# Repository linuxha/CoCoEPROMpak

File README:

CoCoEPROMpak 1.0
Copyright 2013 by Mark J. Blair
Distributed under GPLv3

CoCoEPROMpak is a PCB design for an EPROM-based ROM cartridge for the
Tandy/TRS-80 Color Computer. It can accept on 2732, 2764, 27128, 27256
or 27512 EPROM. Board thickness must be 0.062". Gold plating is
preferable to avoid contact oxidation. Board is designed to the
OSHpark design rules for a 2-layer PCB.

When using 27256 or larger EPROMs, the EPROM is divided into 2-4 16k
banks which can be selected with jumper settings. Jumper settings are
also important for 27256 and smaller EPROMs in order to apply the
correct power and control signals to the EPROM.

4k:
    * Install 2732 at U1
    * JP2, JP3 not used
8k:
    * Install 2764 at U2
    * Set JP2 to 1
    * Set JP3 to 1
16k:
    * Install 27128 at U2
    * Set JP2 to 1
    * Set JP3 to 1
32k:
    * Install 27256 at U2
    * Select 16k bank with JP2
    * Set JP3 to 1
64k:
    * Install 27512 at U2
    * Select 16k banks with JP2 and JP3

CoCoEPROMpak is a free hardware design: you can redistribute it and/or
modify it under the terms of the GNU General Public License as
published by the Free Software Foundation, either version 3 of the
License, or (at your option) any later version.

CoCoEPROMpak is distributed in the hope that it will be useful, but
WITHOUT ANY WARRANTY; without even the implied warranty of
MERCHANTABILITY or FITNESS FOR A PARTICULAR PURPOSE. See the GNU
General Public License for more details.

You should have received a copy of the GNU General Public License
along with CoCoEPROMpak. If not, see <http://www.gnu.org/licenses/>.

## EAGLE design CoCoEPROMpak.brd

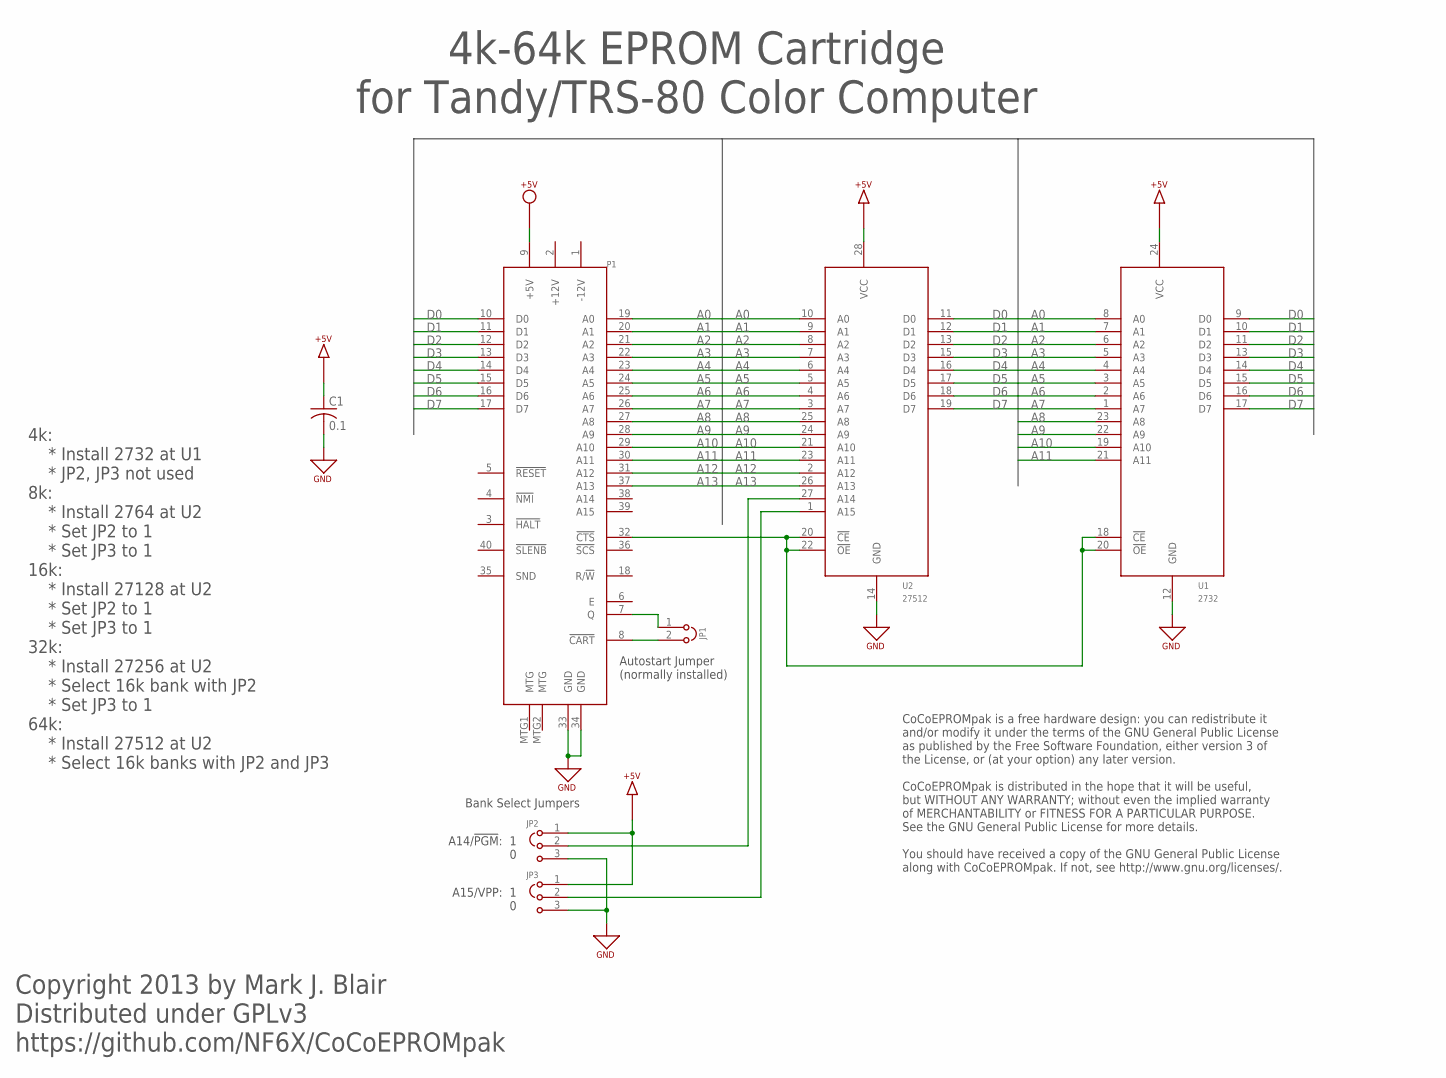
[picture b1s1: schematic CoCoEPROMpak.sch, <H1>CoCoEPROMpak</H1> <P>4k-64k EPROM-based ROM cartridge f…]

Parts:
C1: 0.1; C050-025X075
JP1: JP2; JP2-100MIL
JP2, JP3: JP3; JP3-100MIL
P1: COCO-CART; COCO-CART-2.1X1.75
U1: 2732; DIL24
U2: 27512; DIL28

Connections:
+5V: C1.1, JP2.1, JP3.1, P1.9 (+5V), U1.24 (VCC), U2.28 (VCC)
A0: P1.19 (A0), U1.8 (A0), U2.10 (A0)
A1: P1.20 (A1), U1.7 (A1), U2.9 (A1)
A2: P1.21 (A2), U1.6 (A2), U2.8 (A2)
A3: P1.22 (A3), U1.5 (A3), U2.7 (A3)
A4: P1.23 (A4), U1.4 (A4), U2.6 (A4)
A5: P1.24 (A5), U1.3 (A5), U2.5 (A5)
A6: P1.25 (A6), U1.2 (A6), U2.4 (A6)
A7: P1.26 (A7), U1.1 (A7), U2.3 (A7)
A8: P1.27 (A8), U1.23 (A8), U2.25 (A8)
A9: P1.28 (A9), U1.22 (A9), U2.24 (A9)
A10: P1.29 (A10), U1.19 (A10), U2.21 (A10)
A11: P1.30 (A11), U1.21 (A11), U2.23 (A11)
A12: P1.31 (A12), U2.2 (A12)
A13: P1.37 (A13), U2.26 (A13)
D0: P1.10 (D0), U1.9 (D0), U2.11 (D0)
D1: P1.11 (D1), U1.10 (D1), U2.12 (D1)
D2: P1.12 (D2), U1.11 (D2), U2.13 (D2)
D3: P1.13 (D3), U1.13 (D3), U2.15 (D3)
D4: P1.14 (D4), U1.14 (D4), U2.16 (D4)
D5: P1.15 (D5), U1.15 (D5), U2.17 (D5)
D6: P1.16 (D6), U1.16 (D6), U2.18 (D6)
D7: P1.17 (D7), U1.17 (D7), U2.19 (D7)
GND: C1.2, JP2.3, JP3.3, P1.33 (GND), P1.34 (GND), U1.12 (GND), U2.14 (GND)
unnamed: JP2.2, U2.27 (A14)
unnamed: P1.32 (!CTS), U1.18 (!CE), U1.20 (!OE), U2.20 (!CE), U2.22 (!OE)
unnamed: JP3.2, U2.1 (A15)
unnamed: JP1.2, P1.8 (!CART)
unnamed: JP1.1, P1.7 (Q)

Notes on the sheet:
Autostart Jumper (normally installed)
4k-64k EPROM Cartridge for Tandy/TRS-80 Color Computer
Copyright 2013 by Mark J. Blair Distributed under GPLv3 https://github.com/NF6X/CoCoEPROMpak
Bank Select Jumpers
4k: * Install 2732 at U1 * JP2, JP3 not used 8k: * Install 2764 at U2 * Set JP2 to 1 * Set JP3 to 1 16k: * Install 27128 at U2 * Set JP2 to 1 * Set JP3 to 1 32k: * Install 27256 at U2 * Select 16k bank with JP2 * Set JP3 to 1 64k: * Install 27512 at U2 * Select 16k banks with JP2 and JP3
CoCoEPROMpak is a free hardware design: you can redistribute it and/or modify it under the terms of the GNU General Public License as published by the Free Software Foundation, either version 3 of the License, or (at your option) any later version. CoCoEPROMpak is distributed in the hope that it wi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
A14/!PGM!: 1 0
A15/VPP: 1 0

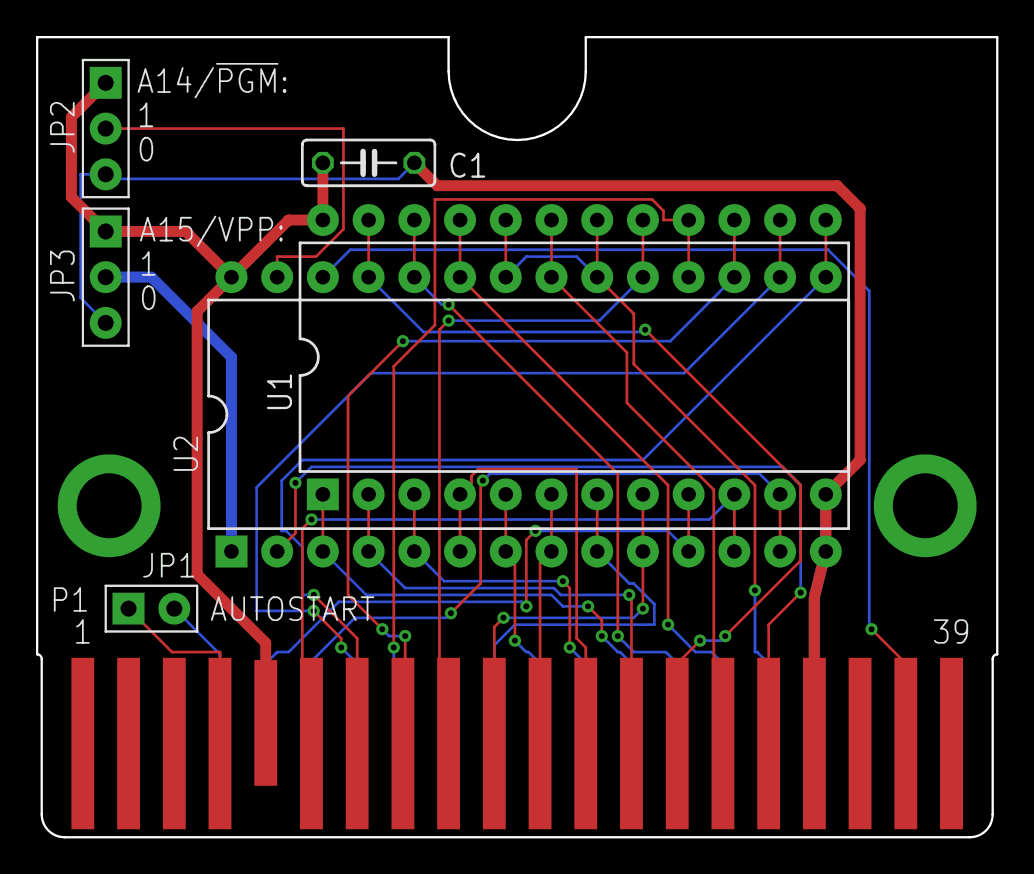
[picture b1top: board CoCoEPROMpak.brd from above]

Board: 2 copper layers, 53.3 x 44.5 mm, 7 parts (0 on the bottom side), 29 nets.

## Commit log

2013-09-26 Initial commit.
2013-09-26 Typo correction.
2013-09-26 Added Gerber outputs. Corrected fonts for proper output.
2013-09-26 Added support for 27256 and 27512 EPROMs with bank-switching by jumper settings.
2013-09-26 New PNGs of draft layout.
2013-09-26 Corrected reference designators in configuration documentation on schematic.
2013-09-27 Documentation improvements.
2017-05-28 Exported project library.

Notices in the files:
CoCoEPROMpak.brd:
Copyright 2013 Mark J. Blair
